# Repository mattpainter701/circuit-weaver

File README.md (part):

<p align="center">

</p>

<p align="center">
  <strong>Programmatic KiCad schematic generation, strict validation, and manufacturing export<br>
  designed for AI-assisted hardware workflows — Claude Code, Codex, and offline CLI.</strong>
</p>

---

## How It Works

The repository also hosts [Weftline 16](asic/slot16/README.md), an experimental embedded processor built on the Slot16 ISA. Its [virtual board](asic/slot16/virtual-board.md) runs the encoder firmware on a desktop with Python.

[Heddle](asic/heddle/README.md) is a second experimental tile: a character language model whose weights are hardwired as logic, with a PCI Express host-card draft and a study of what a much larger hardwired model would need.

Circuit Weaver supports **describe the design → validate → generate KiCad artifacts**, with additional native placement, routing and review workflows. Start from an agent skill or the CLI and inspect the resulting evidence and blockers before proceeding.

### Validated scope

Explore the [interactive routing demos](https://circuit-weaver.com/routing-demos/) to switch between placement and routed copper on three industrial prototype boards, then download the native KiCad files. The pictured Gateway, Relay and Setpoint routes passed KiCad 10.0.4 DRC with zero findings across boards ranging from 187 to 438 footprints.

Circuit Weaver is an **alpha tool for engineering prototypes**. The 0.37.0 workflow corpus covers 13 compact design-spec samples and three connected mixed-signal boards with 149, 155 and 145 physical parts. Each passes 16 stages, including native routing, DRC, assembled model previews and a real MCP session. These are finite regression fixtures; passing them does not establish arbitrary-circuit electrical correctness or fabrication readiness.

Claude Code, Codex and OpenCode can use the packaged agent skills, CLI and optional MCP server. MCP retains its five focused validation and discovery tools and adds runtime inspection plus checkpointed project lifecycle tools. Workflow execution is a synchronous request/response operation; cancellation is observed at stage boundaries. Installer and MCP tests do not constitute a fresh end-to-end test inside every agent client; see [agent platform support](docs/agent-platforms.md).

| Project workflow need | CLI | MCP | Behavior |
|-|-|-|-|
| Check the installed interpreter, capabilities and skill state | `runtime-info --json` | `runtime_info` | Read-only preflight |
| Discover or start a project | `discover --root <dir> --json`, `start <dir> --json` | `discover_projects`, `start_project` | Project paths are explicit for lifecycle operations |
| Open, inspect, and plan work | `open <path> --json`, `workflow plan <dir> --json` | `open_project`, `workflow_status`, `plan_workflow` | Planning does not execute stages |
| Execute or continue checkpointed work | `workflow run <dir>`, `workflow resume <dir>` | `run_workflow`, `resume_workflow` | Stages are validate, generate, build, place, route, preview; checkpoints use input and artifact hashes |
| Request cancellation | `workflow cancel <dir>` | `cancel_workflow` | Cancellation takes effect at the next stage boundary |

See the [project workflow guide](docs/project-workflows.md) for runtime selection, Python functions, MCP configuration, and checkpoint semantics. These tools report only the evidence their completed stages actually produced; they do not grant manufacturing approval.

RF research and circuit-generation assistance are available, but controlled-impedance routing, matching networks, antenna performance and RF stability require separate engineering verification. Native DRC and a rendered board are not evidence of RF performance. Review the [automation validation guide](docs/automation-validation.md) for prerequisites, evidence and prototype delivery gates.

### Reproducible passive SPICE benchmarks

`python benchmarks/diverse_systems/spice_suite.py --output <new-empty-directory>` runs independently defined IoT, SDR IQ, Butterworth, radar IF-bank, megohm/picofarad, and OT burden fixtures through the product SPICE exporter and runner, then compares parsed results with analytic oracles. Ngspice is discovered on `PATH` or selected with `CIRCUIT_WEAVER_NGSPICE` / `--ngspice <executable>`. The suite reports unverified when ngspice is unavailable and labels the OT comparator unverified; its negative controls and passive-model results do not qualify IC models, RF layout, PCB behavior, or manufacturing readiness. See [the benchmark guide](benchmarks/diverse_systems/README.md).

---

<!-- capability-registry:start -->
## Capability Contract

This table is generated from the checked-in capability registry. Regenerate it with `python scripts/gen_capability_docs.py`; do not edit it by hand.

Verification is conservative: a capability only claims the evidence level its public path actually verifies. **not applicable** means an operational capability makes no design-artifact verification claim; it is not a lower verification level.

| CLI capability | Maturity | Public surfaces | Verification contract | Evidence | Since |
|---|---|---|---|---|---|
| `validate` | beta | CLI: `validate`; Python: `circuit_weaver.dispatcher:validate_design`; HTTP: `POST /validate; POST /mvp/validate`; MCP: `validate_design`; Skill: `circuit-weaver` | `static-parse` → `static-parse` | `command-contract`, `static-parse` | 0.32.1 |
| `apply-patch` | beta | CLI: `apply-patch`; Python: `circuit_weaver.dispatcher:apply_design_patch`; HTTP: `POST /mvp/apply-patch` | `static-parse` → `static-parse` | `command-contract`, `static-parse` | 0.32.1 |
| `generate` | experimental | CLI: `generate`; Python: `circuit_weaver.dispatcher:generate_artifacts`; HTTP: `POST /generate; POST /mvp/generate`; MCP: `generate_artifacts`; Skill: `circuit-weaver` | `static-parse` → `static-parse` | `command-contract`, `static-parse`, `kicad-load`, `erc` | 0.32.1 |
| `review-report` | experimental | CLI: `review-report`; Skill: `circuit-weaver` | `static-parse` → `static-parse` | `command-contract`, `static-parse` | 0.32.1 |
| `diff` | beta | CLI: `diff`; Python: `circuit_weaver.dispatcher:diff_designs`; HTTP: `POST /mvp/diff` | `static-parse` → `static-parse` | `command-contract`, `static-parse` | 0.32.1 |
| `ingest-pcb-feedback` | beta | CLI: `ingest-pcb-feedback`; Python: `circuit_weaver.dispatcher:ingest_pcb_feedback`; HTTP: `POST /mvp/pcb-feedback` | `static-parse` → `static-parse` | `command-contract`, `static-parse` | 0.32.1 |
| `import-placement` | review_only | CLI: `import-placement`; Skill: `circuit-weaver` | `static-parse` → `static-parse` | `command-contract`, `static-parse` | 0.32.1 |
| `list-templates` | beta | CLI: `list-templates`; HTTP: `GET /templates` | not applicable (operational) | `command-contract` | 0.32.1 |
| `scaffold` | beta | CLI: `scaffold`; Skill: `circuit-weaver` | `static-parse` → `static-parse` | `command-contract`, `static-parse` | 0.32.1 |
| `register-ic` | experimental | CLI: `register-ic` | `static-parse` → `static-parse` | `command-contract`, `static-parse` | 0.32.1 |
| `resolve-symbol` | experimental | CLI: `resolve-symbol` | not applicable (operational) | `command-contract` | 0.33.0 |
| `adopt` | experimental | CLI: `adopt`; Python: `circuit_weaver.project_workflow:adopt_project`; MCP: `adopt_project`; Skill: `circuit-weaver` | not applicable (operational) | `command-contract` | 0.38.0 |
| `library-bundle` | experimental | CLI: `library-bundle`; Python: `circuit_weaver.library_bundle:plan_library_bundle`; MCP: `plan_library_bundle; apply_library_bundle`; Skill: `circuit-weaver` | not applicable (operational) | `command-contract` | 0.38.0 |
| `export-jlcpcb` | review_only | CLI: `export-jlcpcb`; Skill: `circuit-weaver` | `static-parse` → `static-parse` | `command-contract`, `static-parse` | 0.32.1 |
| `export-gerbers` | review_only | CLI: `export-gerbers`; Skill: `circuit-weaver` | `static-parse` → `static-parse` | `command-contract`, `static-parse` | 0.32.1 |
| `cost-bom` | experimental | CLI: `cost-bom`; Skill: `circuit-weaver` | `static-parse` → `static-parse` | `command-contract`, `static-parse` | 0.32.1 |
| `import-design` | experimental | CLI: `import-design`; Python: `circuit_weaver.design_import:import_design`; Skill: `circuit-weaver` | `static-parse` → `static-parse` | `command-contract`, `static-parse` | 0.32.1 |
| `analyze-design` | experimental | CLI: `analyze-design`; Python: `circuit_weaver.design_import:analyze_design`; Skill: `circuit-weaver` | `static-parse` → `static-parse` | `command-contract`, `static-parse` | 0.32.1 |
| `status` | beta | CLI: `status`; Python: `circuit_weaver.project_state:get_project_state_summary`; Skill: `circuit-weaver` | not applicable (operational) | `command-contract` | 0.32.1 |
| `resume` | experimental | CLI: `resume`; Python: `circuit_weaver.project_state:resume_project`; Skill: `circuit-weaver` | not applicable (operational) | `command-contract` | 0.32.1 |
| `design-wizard` | experimental | CLI: `design-wizard`; Skill: `design-wizard` | `static-parse` → `static-parse` | `command-contract`, `static-parse` | 0.32.1 |
| `build-pcb` | experimental | CLI: `build-pcb`; Python: `circuit_weaver.schematic_pcb:schematic_to_pcb`; Skill: `circuit-weaver` | `static-parse` → `kicad-load` | `command-contract`, `static-parse`, `kicad-load`, `external-tool` | 0.35.0 |
| `place-pcb` | experimental | CLI: `place-pcb`; Skill: `circuit-weaver` | `static-parse` → `static-parse` | `command-contract`, `external-tool`, `user-supplied` | 0.32.1 |
| `review-pcb` | review_only | CLI: `review-pcb`; Python: `circuit_weaver.board_review:review_pcb`; MCP: `review_board`; Skill: `circuit-weaver` | `static-parse` → `kicad-load` | `command-contract`, `external-tool`, `user-supplied` | 0.38.0 |
| `plane-pcb` | review_only | CLI: `plane-pcb`; Python: `circuit_weaver.pcb_ground_plane:add_ground_plane`; Skill: `circuit-weaver` | `static-parse` → `kicad-load` | `command-contract`, `kicad-load`, `external-tool`, `user-supplied` | 0.35.0 |
| `plane-cleanup-pcb` | review_only | CLI: `plane-cleanup-pcb`; Python: `circuit_weaver.pcb_plane_cleanup:cleanup_plane_traces`; Skill: `circuit-weaver` | `static-parse` → `kicad-load` | `command-contract`, `kicad-load`, `external-tool`, `user-supplied` | 0.35.0 |
| `cleanup-pcb` | review_only | CLI: `cleanup-pcb`; Python: `circuit_weaver.pcb_copper_cleanup:cleanup_copper`; Skill: `circuit-weaver` | `static-parse` → `kicad-load` | `command-contract`, `kicad-load`, `external-tool`, `user-supplied` | 0.35.0 |
| `refine-pcb` | review_only | CLI: `refine-pcb`; Python: `circuit_weaver.pcb_return_paths:refine_return_paths`; Skill: `circuit-weaver` | `static-parse` → `kicad-load` | `command-contract`, `kicad-load`, `external-tool`, `user-supplied` | 0.35.0 |
| `preview-pcb` | review_only | CLI: `preview-pcb`; Python: `circuit_weaver.pcb_preview:render_board_preview`; Skill: `circuit-weaver` | `static-parse` → `kicad-load` | `command-contract`, `static-parse`, `kicad-load`, `external-tool` | 0.35.0 |
| `log-status` | beta | CLI: `log-status` | not applicable (operational) | `command-contract` | 0.32.1 |
| `log-view` | beta | CLI: `log-view` | not applicable (operational) | `command-contract` | 0.32.1 |
| `autoroute` | review_only | CLI: `autoroute`; Skill: `circuit-weaver` | `static-parse` → `static-parse` | `command-contract`, `external-tool`, `user-supplied` | 0.32.1 |
| `install-skills` | experimental | CLI: `install-skills` | not applicable (operational) | `command-contract` | 0.32.1 |
| `schema` | beta | CLI: `schema` | not applicable (operational) | `command-contract` | 0.32.1 |
| `harvest-specs` | experimental | CLI: `harvest-specs` | `static-parse` → `static-parse` | `command-contract`, `external-tool` | 0.32.1 |
| `extract-specs` | experimental | CLI: `extract-specs` | `static-parse` → `static-parse` | `command-contract`, `user-supplied` | 0.32.1 |
| `fetch-spice` | experimental | CLI: `fetch-spice` | `static-parse` → `static-parse` | `command-contract`, `external-tool` | 0.32.1 |
| `cache` | beta | CLI: `cache` | not applicable (operational) | `command-contract` | 0.32.1 |
| `cache stats` | beta | CLI: `cache stats` | not applicable (operational) | `command-contract` | 0.32.1 |
| `cache clear` | review_only | CLI: `cache clear` | not applicable (operational) | `command-contract` | 0.32.1 |
| `optimize-placement` | review_only | CLI: `optimize-placement`; Skill: `circuit-weaver` | `static-parse` → `static-parse` | `command-contract`, `static-parse` | 0.32.1 |
| `placement-viewer` | review_only | CLI: `placement-viewer`; Skill: `circuit-weaver` | `static-parse` → `static-parse` | `command-contract`, `static-parse` | 0.32.1 |
| `si-constraints` | experimental | CLI: `si-constraints` | `static-parse` → `static-parse` | `command-contract`, `static-parse` | 0.32.1 |
| `thermal-analysis` | experimental | CLI: `thermal-analysis` | `static-parse` → `static-parse` | `command-contract`, `static-parse` | 0.32.1 |
| `export-dual-cpl` | review_only | CLI: `export-dual-cpl` | `static-parse` → `static-parse` | `command-contract`, `static-parse` | 0.32.1 |
| `panelize` | experimental | CLI: `panelize` | `static-parse` → `static-parse` | `command-contract`, `static-parse` | 0.32.1 |
| `design-enclosure` | experimental | CLI: `design-enclosure` | `static-parse` → `static-parse` | `command-contract`, `static-parse` | 0.32.1 |
| `check-dfm` | review_only | CLI: `check-dfm` | `static-parse` → `static-parse` | `command-contract`, `static-parse` | 0.32.1 |
| `generate-docs` | experimental | CLI: `generate-docs` | `static-parse` → `static-parse` | `command-contract`, `static-parse` | 0.32.1 |
| `erc` | review_only | CLI: `erc` | `kicad-load` → `erc` | `command-contract`, `kicad-load`, `erc` | 0.32.1 |
| `doctor` | beta | CLI: `doctor` | not applicable (operational) | `command-contract` | 0.32.1 |
| `repair` | experimental | CLI: `repair`; Python: `circuit_weaver.repair_service:apply_no_connect` | `static-parse` → `static-parse` | `command-contract`, `static-parse` | 0.35.0 |
| `confidence` | review_only | CLI: `confidence`; Skill: `circuit-weaver` | `static-parse` → `static-parse` | `command-contract`, `static-parse` | 0.32.1 |
| `manufacturing-readiness` | beta | CLI: `manufacturing-readiness`; Python: `circuit_weaver.manufacturing_readiness:read_manufacturing_readiness`; HTTP: `POST /manufacturing-readiness`; MCP: `manufacturing_readiness`; Skill: `circuit-weaver` | `static-parse` → `static-parse` | `command-contract`, `fabrication-ready` | 0.34.0 |
| `simulate` | experimental | CLI: `simulate`; Skill: `circuit-weaver` | `static-parse` → `static-parse` | `command-contract`, `static-parse` | 0.32.1 |
| `discover` | beta | CLI: `discover`; MCP: `discover_projects`; Skill: `circuit-weaver` | not applicable (operational) | `command-contract` | 0.32.1 |
| `start` | beta | CLI: `start`; Python: `circuit_weaver.project_workflow:start_project`; MCP: `start_project`; Skill: `circuit-weaver` | not applicable (operational) | `command-contract` | unreleased |
| `open` | beta | CLI: `open`; Python: `circuit_weaver.project_workflow:open_project`; MCP: `open_project`; Skill: `circuit-weaver` | not applicable (operational) | `command-contract` | unreleased |
| `runtime-info` | beta | CLI: `runtime-info`; Python: `circuit_weaver.runtime_info:runtime_info`; MCP: `runtime_info`; Skill: `circuit-weaver` | not applicable (operational) | `command-contract` | unreleased |
| `workflow` | beta | CLI: `workflow`; Skill: `circuit-weaver` | not applicable (operational) | `command-contract` | unreleased |
| `workflow plan` | beta | CLI: `workflow plan`; Python: `circuit_weaver.project_workflow:plan_workflow`; MCP: `plan_workflow`; Skill: `circuit-weaver` | not applicable (operational) | `command-contract` | unreleased |
| `workflow run` | beta | CLI: `workflow run`; Python: `circuit_weaver.project_workflow:run_workflow`; MCP: `run_workflow`; Skill: `circuit-weaver` | not applicable (operational) | `command-contract` | unreleased |
| `workflow status` | beta | CLI: `workflow status`; Python: `circuit_weaver.project_workflow:workflow_status`; MCP: `workflow_status`; Skill: `circuit-weaver` | not applicable (operational) | `command-contract` | unreleased |
| `workflow resume` | beta | CLI: `workflow resume`; Python: `circuit_weaver.project_workflow:resume_workflow`; MCP: `resume_workflow`; Skill: `circuit-weaver` | not applicable (operational) | `command-contract` | unreleased |
| `workflow cancel` | beta | CLI: `workflow cancel`; Python: `circuit_weaver.project_workflow:cancel_workflow`; MCP: `cancel_workflow`; Skill: `circuit-weaver` | not applicable (operational) | `command-contract` | unreleased |
| `library-access` | beta | CLI: `library-access`; Python: `circuit_weaver.library_access:audit_library_access`; MCP: `library_access`; Skill: `circuit-weaver` | not applicable (operational) | `command-contract` | unreleased |
| `silicon` | review_only | CLI: `silicon` | not applicable (operational) | `command-contract` | unreleased |
| `silicon preview` | review_only | CLI: `silicon preview`; Python: `circuit_weaver.silicon_preview:render_silicon_preview`; MCP: `silicon_preview` | `static-parse` → `static-parse` | `command-contract`, `external-tool`, `user-supplied` | unreleased |
| `silicon handoff` | review_only | CLI: `silicon handoff`; Python: `circuit_weaver.silicon_handoff:review_silicon_handoff`; MCP: `silicon_handoff` | `static-parse` → `static-parse` | `command-contract`, `external-tool`, `user-supplied` | unreleased |
| `silicon slot-map` | review_only | CLI: `silicon slot-map`; Python: `circuit_weaver.tt_slot:map_tt_slot`; MCP: `silicon_slot_map` | `static-parse` → `static-parse` | `command-contract`, `external-tool`, `user-supplied` | unreleased |
| `save-research` | experimental | CLI: `save-research`; Skill: `circuit-weaver` | `static-parse` → `static-parse` | `command-contract`, `static-parse` | 0.32.1 |
| `log-event` | beta | CLI: `log-event` | not applicable (operational) | `command-contract` | 0.32.1 |
<!-- capability-registry:end -->

## Quick Start

**Step 1 — Install**

```bash
pip install circuit-weaver
```

**Step 2 — Register the skill** *(one-time, for Claude Code / Codex / OpenCode)*

```bash
circuit-weaver install-skills            # install for all supported agent platforms
circuit-weaver install-skills --dry-run  # preview without touching disk
circuit-weaver install-skills --force --backup   # resolve conflicts, back up every replaced file
```

> **Upgrade safety:** each installed skill has a provenance manifest containing hashes for every
> managed file. A pristine older release upgrades automatically. A file changed or deleted by the
> user is preserved and reported as a conflict, and the command exits non-zero. Pass `--force`
> only after reviewing conflicts; add `--backup` to preserve every replaced file.

**Step 3 — Launch**

```text
# Claude Code:
/circuit-weaver

# Codex:
$circuit-weaver

# OpenCode: ask it to use circuit-weaver (loaded through its skill tool).

# Or run offline without any agent:
circuit-weaver design-wizard
```

The skill walks through IC selection, spec validation, schematic generation, and the electrical-PCB handoff.

For a repeatable real-tool demonstration, run `python scripts/validate_app_workflow.py --output ./workflow-evidence`.
The [automation validation guide](docs/automation-validation.md) describes native ERC/DRC evidence, optional MCP checks,
and the prototype/manufacturing boundary.

---

## Research Traceability

Agentic research runs are expected to persist their output into `output/research/`.
That directory is the source of truth for why an IC was chosen, which citations
backed it, and which backend produced the result.

For Codex / Claude / OpenCode workflows, Step 2 IC research should stay in the
current agent session. If a premium-research command would delegate to a
subagent or fails with a model/tool conflict, use the platform's native web
tools instead and persist the backend that actually ran.

```bash
# Check which backend and depth are active before research starts
circuit-weaver doctor

# Optional: force backend/depth selection for agent workflows
export CIRCUIT_WEAVER_RESEARCH_BACKEND=standard   # or sonar-pro / auto
export CIRCUIT_WEAVER_RESEARCH_DEPTH=fast         # or normal
# PowerShell: $env:CIRCUIT_WEAVER_RESEARCH_BACKEND="standard"
# PowerShell: $env:CIRCUIT_WEAVER_RESEARCH_DEPTH="fast"

# Persist a completed research result
circuit-weaver save-research --project-dir ./output --file research.json
```

Each saved run produces `{slug}.json`, `{slug}.md`, and `summary.md`, and the
matching `design.log` entry records the canonical JSON path for later audit.

---

## Branch Maintenance

Use `scripts/cleanup_branches.py` to audit stale local branches before pruning them.
The command is dry-run by default and only targets merged, unprotected branches,
so dated work can be reviewed without risking useful code. When run with
`--delete`, deleted branch tips are archived under `refs/archive/branches/<name>`
unless `--no-archive` is explicitly supplied.

```bash
python scripts/cleanup_branches.py                 # audit only
python scripts/cleanup_branches.py --delete        # prune merged stale branches and keep archives
python scripts/cleanup_branches.py --force-unmerged # include unmerged branches only when intentionally forced
```

---

## What You Get

A successful default `generate` run produces a complete artifact bundle
(`--no-placement-review` deliberately omits the four placement-review files):

| Artifact | File | Description |
|-|-|-|
| KiCad schematic hierarchy | `{project}.kicad_sch` plus functional sub-sheets | Real, loadable hierarchy; explicit block `section` values remain separate professional sheets and support passives follow their owner |
| Markdown design report | `{project}_report.md` | Validation results, component summary, and design notes |
| Placement review | `placement_result.json`, `placement_review_context.json`, `placement.svg`, `placement_editor.html` | Exhaustive, reference-reconciled heuristic proposal with review blockers and official-reference context; never fabrication data |
| Assembly inventory | `assembly_manifest.json` | Stable physical-part references, including generated support passives |
| Evidence ledger | `evidence_manifest.json` | Stable component, pinout, footprint, parameter, finding, tool, and verification provenance IDs |
| Canonical spec and IR | `canonical_spec.yaml`, `design_ir.json` | Normalized source of truth and generated design IR |
| Validation evidence | `validation_report.json`, `placement_readiness.json` | Machine-readable release/readiness checks |
| Artifact inventory | `artifact_manifest.json` | Portable relative paths, verification state, kinds, and sizes for every generated artifact |
| Test point map | `{project}_test_points.csv` | Auto-detected power, clock, bus, and differential-pair nets |
| Firmware stubs (when applicable) | `{project}_pinout.csv`, `.ioc`, `sdkconfig.defaults` | MCU pin map and STM32/ESP32 co-design files |

---

## Resume or Analyze an Existing Design

Circuit Weaver keeps restartable state in `<project>/.circuit-weaver/project.json`.
Import is non-destructive: source KiCad, PCB, Gerber, drill, and ZIP files are
inventoried and hashed rather than regenerated.

```bash
# Import a KiCad project, a single KiCad file, a Gerber directory, or a ZIP
circuit-weaver import-design ./existing_board --analyze

# Inspect durable state or get a deterministic restart plan
circuit-weaver status ./existing_board
circuit-weaver resume ./existing_board

# Re-run every applicable bundled analyzer; unchanged results are cached
circuit-weaver analyze-design ./existing_board
```

Use `--project-dir <dir>` when state should live somewhere other than the
source directory. Use `--force` only to intentionally replace a changed import
source set, ZIP staging tree, or cached analysis. Netlist-only imports are
inventoried, but analysis is reported as unsupported because a netlist alone
does not contain schematic or physical-layout evidence.

### Bounded no-connect repair

The first experimental imported-design repair is deliberately narrow: it can
add one explicit KiCad no-connect marker only when a
`circuit-weaver-repair-metadata/v1` envelope binds the exact source hash,
analyzer component/pin identity, a v2 finding, and its validated evidence
manifest. Build that envelope with
`circuit_weaver.repair_service.build_no_connect_metadata`; the matching trusted
finding producer is `no_connect_finding_from_intent`. Both require current,
verified user evidence whose exact `pin:REF.NUMBER` claim says the pin is
intentionally unused. Raw analyzer JSON or an unbound boolean is rejected.

The service then independently proves the component UUID/library ID, pin
coordinate, and absence of a net, wire, label, junction, bus entry,
hierarchical sheet pin, power symbol, or coincident component pin. The plan is
reviewable JSON; the apply step will not infer approval from that file.

```bash
circuit-weaver repair suggest board.kicad_sch repair-metadata.json \
  --ref U1 --pin 4 \
  --finding-id FND-0123456789ab \
  --evidence-id EV-VALIDATION-0123456789ab \
  --output no-connect-plan.json

# Review the plan and copy its plan_sha256 through the approval channel.
circuit-weaver repair apply no-connect-plan.json repair-metadata.json \
  --approved-plan-hash <approved-plan-sha256> \
  --reviewer <reviewer> \
  --finding-id FND-0123456789ab \
  --evidence-id EV-VALIDATION-0123456789ab

circuit-weaver repair verify board.kicad_sch no-connect-plan.json
```

The public capability guarantee is static parsing. Run KiCad ERC after review;
unsupported topology, geometry, part replacement, and pin-remapping repairs
fail closed instead of being improvised. Apply holds cross-process source and
audit locks, keeps an exact hard-linked preimage through publication, and uses
prepared/committed append-only audit events so an interrupted successful
publication can be recovered on retry. Lock hardlinks and reparse aliases are
rejected before mutation; the default audit sidecar cannot escape through a
directory junction. On Windows, atomic replacement preserves and verifies the
target owner, group, and DACL access semantics. Applications that write
schematics without honoring Circuit Weaver's lock remain outside the
cooperative locking contract; snapshot, identity, and post-image checks still
detect ordinary write races and preserve observed user bytes rather than
rolling over them.

---

## PCB Placement Workflow

Circuit Weaver generates a review-only placement proposal, then KiCad creates
the electrical PCB. The SVG/HTML/JSON proposal is never a PCB, CPL, or other
fabrication artifact.

### 1 — Generate initial placement

`generate` returns the path to `artifact_manifest.json`. Resolve that manifest's portable `root_schematic` and artifact paths relative to the manifest directory instead of guessing filenames. Check `verification_status` before claiming KiCad verification. Placement review is enabled by default:

```bash
circuit-weaver generate design.yaml -o ./output
# → output/{project}.kicad_sch
# → output/placement_result.json
# → output/placement_review_context.json
# → output/placement.svg
# → output/placement_editor.html
# → output/{project}_report.md
```

`placement_result.json` must contain the exact `assembly_manifest.json`
reference inventory. It remains `fabrication_ready: false` by design. Review
its overlap, boundary, support-part, geometry, sourcing, and constraint
blockers. `placement_review_context.json` records constraints, targeted
research prompts, and official component/reference-layout links available to
the agent; manufacturer documentation remains authoritative.

### 2 — Optimize with simulated annealing

```bash
# Basic optimization (5 000 iterations, reproducible with seed)
circuit-weaver optimize-placement design.yaml --iterations 5000 --seed 42 \
    -o output/placement.json

# Thermal-aware strategy (minimizes hotspot proximity)
circuit-weaver optimize-placement design.yaml --strategy thermal --iterations 10000 \
    -o output/placement.json

# Read component thermal/SI specs from YAML files
circuit-weaver optimize-placement design.yaml --specs-dir ./specs/
```

The optimizer minimizes: overlap, boundary violations, thermal clustering, and DFM zone penalties via simulated annealing. Returns a placement JSON with x/y/rotation/layer per component.

### 3 — Review in the interactive viewer

Open the generated `output/placement_editor.html`, or generate a standalone
viewer for a different optimizer configuration:

```bash
circuit-weaver placement-viewer design.yaml -o output/viewer.html
```

Opens a self-contained HTML file with:
- Click-to-highlight nets
- Component hover tooltips (value, footprint, MPN)
- Thermal heatmap overlay (blue → red gradient by power dissipation)
- CSV export button for placement data

### 4 — Create the electrical PCB in KiCad

Open `artifact_manifest.json`, then open its `root_schematic`, assign and verify footprints, and run **Update PCB from Schematic**. Save that electrically annotated board under a separate name. Only this board has the pads and nets required by routing, DFM, and Gerber export.

Apply reviewed SVG coordinates only to that real electrical PCB. The default
import is strict: every PCB reference must appear exactly once in the SVG, and
unexpected or missing references block the write.

```bash
circuit-weaver import-placement output/placement.svg board.kicad_pcb \
    -o board_placed.kicad_pcb --dry-run
circuit-weaver import-placement output/placement.svg board.kicad_pcb \
    -o board_placed.kicad_pcb

# Intentional subset update only; unknown SVG references still fail.
circuit-weaver import-placement subset.svg board.kicad_pcb \
    -o board_placed.kicad_pcb --allow-partial
```

### 5 — Place and route the real board

After forward annotation, add a rectangular Edge.Cuts outline and lock connectors
that must remain fixed. Place the actual library footprints, route, import the
tracks, and check the final PCB:

```bash
circuit-weaver place-pcb board.kicad_pcb -o board_placed.kicad_pcb --seed 7
circuit-weaver autoroute board_placed.kicad_pcb --attempts 3 \
    --routed-board board_routed.kicad_pcb
circuit-weaver preview-pcb board_routed.kicad_pcb -o board-preview.svg
```

The preview draws actual board layers and footprint body geometry. Use `--side back`
for a mirrored underside or `--render-3d` for a native assembly-model PNG on KiCad 9+
with the declared model files installed. The [workflow demo](docs/automation-validation.md)
includes named preview controls and full-size views.

KiCad's native Python is discovered separately from your application Python.
Freerouting and a compatible Java runtime are required for routing. The input
board must have real pads and nets; padless previews are rejected. Placement
currently requires an unrouted rectangular board without zones. It preserves
locked footprints and board sides, uses real courtyards and rotated pad locations,
and checks physical DRC. Routing publishes the final board only after KiCad DRC
passes, preserving project rules. See [setup and limits](docs/routing-placement-search.md).

For custom footprint installations, set `KICAD_FOOTPRINT_DIR` or the matching
`KICAD10_FOOTPRINT_DIR`, `KICAD9_FOOTPRINT_DIR`, or `KICAD8_FOOTPRINT_DIR`.
An explicit library root takes precedence. Known bare package names use the same
library-prefix mapping during validation and generation; custom references must
still resolve exactly.

Native placement permits overlapping front/back SMD body projections only when
the pad and copper-layer inventory proves separate surfaces and no opposite-side
courtyard is present. Through-hole and unknown geometry remain blocking. This
does not establish 3D enclosure clearance or signal integrity.

With complete native pad maps, decoupling refinement considers position and
quarter-turn rotation together around the owner's supply and return pads.
Candidates must improve the existing placement rank while preserving constraints,
board sides, both local power-leg distances and global power-net spans. These
geometric checks still require native label checks, routing and final DRC; they
do not establish routed loop inductance or electrical performance.

For imported boards with a legacy `.pro` project, convert and verify the project
rules in KiCad before placement, routing, or copper edits. These operations
require a sibling `.kicad_pro` when `.pro` exists; upgrading the PCB format alone
does not migrate those rules. Read-only inspection and previews remain available.

Each Freerouting attempt saves stdout, stderr, the actual input board design
(DSN), and an `attempt.json` manifest under `.circuit-weaver-router-logs` beside
the requested session. The manifest records the command and the input SHA-256.
Full logs stay on disk. Returned diagnostics use bounded windows and missing
final statistics remain unverified. The DSN contains the board geometry and
netlist. Keep this directory local when sharing a project.

PCB handoff manifests distinguish requested constraints from emitted KiCad rules.
DDR interfaces retain explicit unverified requirements for device timing,
topology, signal roles and stackup. Rule rendering and ordinary DRC do not
establish DDR timing closure or controlled impedance.

### 6 — DFM check and panelization

```bash
# Check static track/via dimensions; native KiCad DRC is also required
circuit-weaver check-dfm electrical_board.kicad_pcb --profile jlcpcb

# Get panel layout suggestions for small boards
circuit-weaver panelize --board-width 50 --board-height 40 --qty 100

# Export dual-sided CPL (top + bottom)
circuit-weaver export-dual-cpl design.yaml --pcb electrical_board.kicad_pcb -o ./jlcpcb

# Export a reconciled JLCPCB delivery and inspect its commit manifest
circuit-weaver export-jlcpcb design.yaml --pcb electrical_board.kicad_pcb -o ./jlcpcb
# → bom_jlcpcb.csv, cpl_jlcpcb.csv, README_jlcpcb.txt, delivery_manifest.json
```

Without `--pcb`, `export-jlcpcb` is intentionally BOM-only. A supplied board
must match every assembly reference and footprint before CPL publication.
Treat `delivery_manifest.json` as the delivery status/commit marker.

---

## CLI Reference

```bash
# ── Design lifecycle ──────────────────────────────────────────────────────────
circuit-weaver validate design.yaml               # Validate spec (no files written)
circuit-weaver generate design.yaml -o ./output  # Full artifact bundle
circuit-weaver erc output/{project}.kicad_sch      # Use root_schematic from artifact_manifest.json
circuit-weaver diff old.yaml new.yaml             # Semantic diff + optional SVG
circuit-weaver import-design ./legacy_board --analyze
circuit-weaver status ./legacy_board
circuit-weaver resume ./legacy_board
circuit-weaver analyze-design ./legacy_board

# ── Placement ─────────────────────────────────────────────────────────────────
circuit-weaver optimize-placement design.yaml --iterations 5000 --seed 42 -o output/placement.json
circuit-weaver placement-viewer design.yaml -o output/viewer.html
circuit-weaver import-placement placement.svg board.kicad_pcb -o out.kicad_pcb
circuit-weaver import-placement subset.svg board.kicad_pcb -o out.kicad_pcb --allow-partial
circuit-weaver check-dfm electrical_board.kicad_pcb --profile jlcpcb
circuit-weaver panelize --board-width 50 --board-height 40 --qty 100
circuit-weaver export-dual-cpl design.yaml --pcb electrical_board.kicad_pcb -o ./jlcpcb

# ── Simulation & confidence ──────────────────────────────────────────────────
circuit-weaver simulate design.yaml -o ./sims      # Run SPICE simulations (ngspice)
circuit-weaver confidence design.yaml --run-sims   # Full design readiness score (0-100)
circuit-weaver confidence design.yaml -o report.html --pcb board.kicad_pcb

# ── BOM and manufacturing ─────────────────────────────────────────────────────
circuit-weaver cost-bom design.yaml --qty 1,10,100
circuit-weaver export-jlcpcb design.yaml --pcb electrical_board.kicad_pcb -o ./jlcpcb
circuit-weaver export-gerbers electrical_board.kicad_pcb -o ./gerbers

# ── Project management ───────────────────────────────────────────────────────
circuit-weaver discover                             # Auto-detect projects in CWD
circuit-weaver discover --json --depth 2            # JSON output, search 2 levels deep
circuit-weaver save-research --project-dir ./output --file research.json
circuit-weaver log-event ./project --type scoring --message "Review done"
circuit-weaver doctor                               # Check credentials, backends, and tool availability

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
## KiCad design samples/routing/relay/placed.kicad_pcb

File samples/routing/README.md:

# KiCad routing samples

Open a **routed** board in KiCad 10 PCB Editor to inspect the copper, or use its
**placed** board to try a different routing policy on the same footprint and
reference-label positions. Keep each board beside its same-named `.kicad_pro`
so KiCad loads the original net classes. These are two-layer prototype layouts
for placement, routing and repair experiments.

| Board | What to inspect | KiCad files | Vias | Copper |
| --- | --- | --- | ---: | ---: |
| **Facility gateway** · 187 footprints | Eight analog acquisition channels share the board with RS-485 and CAN. The full and first-clean policies produced identical copper in all three paired runs. | [Placed](gateway/placed.kicad_pcb) · [Routed](gateway/routed.kicad_pcb) · [Project files](gateway/) | 214 | 10,328.81 mm |
| **Serial relay output card** · 268 footprints | Follow the register-to-driver-to-header routing on 160 coil channels. The pictured first-clean route used 19 more vias than its paired full-portfolio run. | [Placed](relay/placed.kicad_pcb) · [Routed](relay/routed.kicad_pcb) · [Project files](relay/) | 839 | 27,749.30 mm |
| **Analog setpoint card** · 438 footprints | Follow the shared SPI bus to 36 dual DACs and the filters serving 72 outputs. The saved partial below isolates one open on that bus. | [Placed](setpoint/placed.kicad_pcb) · [Routed](setpoint/routed.kicad_pcb) · [Project files](setpoint/) | 530 | 20,433.41 mm |

| Facility gateway | Serial relay | Analog setpoint |
| --- | --- | --- |
|  |  |  |

Orange traces are front copper and blue traces are back copper. Each preview
shows its linked routed file. The lengths above sum native track and arc
lengths on both layers. Each of these three files passed KiCad 10.0.4 DRC with
zero findings and passed its signal and return-path checks (43, 160 and 110
paths respectively).

## Replay a route

From the repository root, copy a placement and its project into an empty
working directory. This example uses Gateway. The study used KiCad 10.0.4
and Freerouting 2.5.0 with the following settings.

```sh
mkdir gateway-trial
cp samples/routing/gateway/placed.kicad_pcb gateway-trial/
cp samples/routing/gateway/placed.kicad_pro gateway-trial/
cd gateway-trial
circuit-weaver autoroute placed.kicad_pcb --routed-board result.kicad_pcb --attempts 3 --timeout 1800 --max-passes 20 --optimization-threads 0 --repair-open-connections --recovery-timeout 1800 --stop-at-first-clean
kicad-cli pcb drc --format json --severity-all --exit-code-violations -o result-drc.json result.kicad_pcb
```

For a full-portfolio comparison, repeat in a second empty directory with the
same inputs and omit `--stop-at-first-clean`. Independent runs can choose
different routes. The gallery preserves the representative first-clean outputs
from Gateway repeat 3, Relay repeat 1 and Setpoint repeat 3. The study reports
the medians across all three repeats. [Routing study and timings](https://github.com/mattpainter701/circuit-weaver/pull/63)
· [Tool setup](../../docs/routing-placement-search.md#tool-setup)

## Inspect the last Setpoint open

Open [last-open.kicad_pcb](setpoint/last-open.kicad_pcb) with its
[project settings](setpoint/last-open.kicad_pro). Run DRC and select the single
unconnected item to zoom to pad **U54.7** and the **F.Cu** track on
`SPI_MOSI`. This snapshot comes from repair of a partial session on the same
placement. It closed 107 of 108 opens. The independent clean route in the
gallery shows one way the full-board router connected that net.
[Compare the two SPI_MOSI routes at the same scale](setpoint/spi-mosi.svg)

From the repository root, replay stock repair with the remaining time budget.
The command writes fresh DRC and recovery evidence into a new directory.

```sh
python benchmarks/general_scale/replay_routing_repair.py samples/routing/setpoint/last-open.kicad_pcb --output setpoint-replay --recovery-seconds 104.4 --pair-limit 0
```

The recorded baseline ended with one open and zero other DRC findings. The
replay output records the remaining opens and whether a clean board was
published. [Repair study](https://github.com/mattpainter701/circuit-weaver/pull/64)
· [Replay options](../../benchmarks/general_scale/README.md#replay-routing-repair)

The designs and path contracts come from Circuit Weaver's
[unseen-scale fixtures](../../benchmarks/unseen_scale/README.md).
[SHA256SUMS](SHA256SUMS) identifies the exact PCB and project files in this gallery.

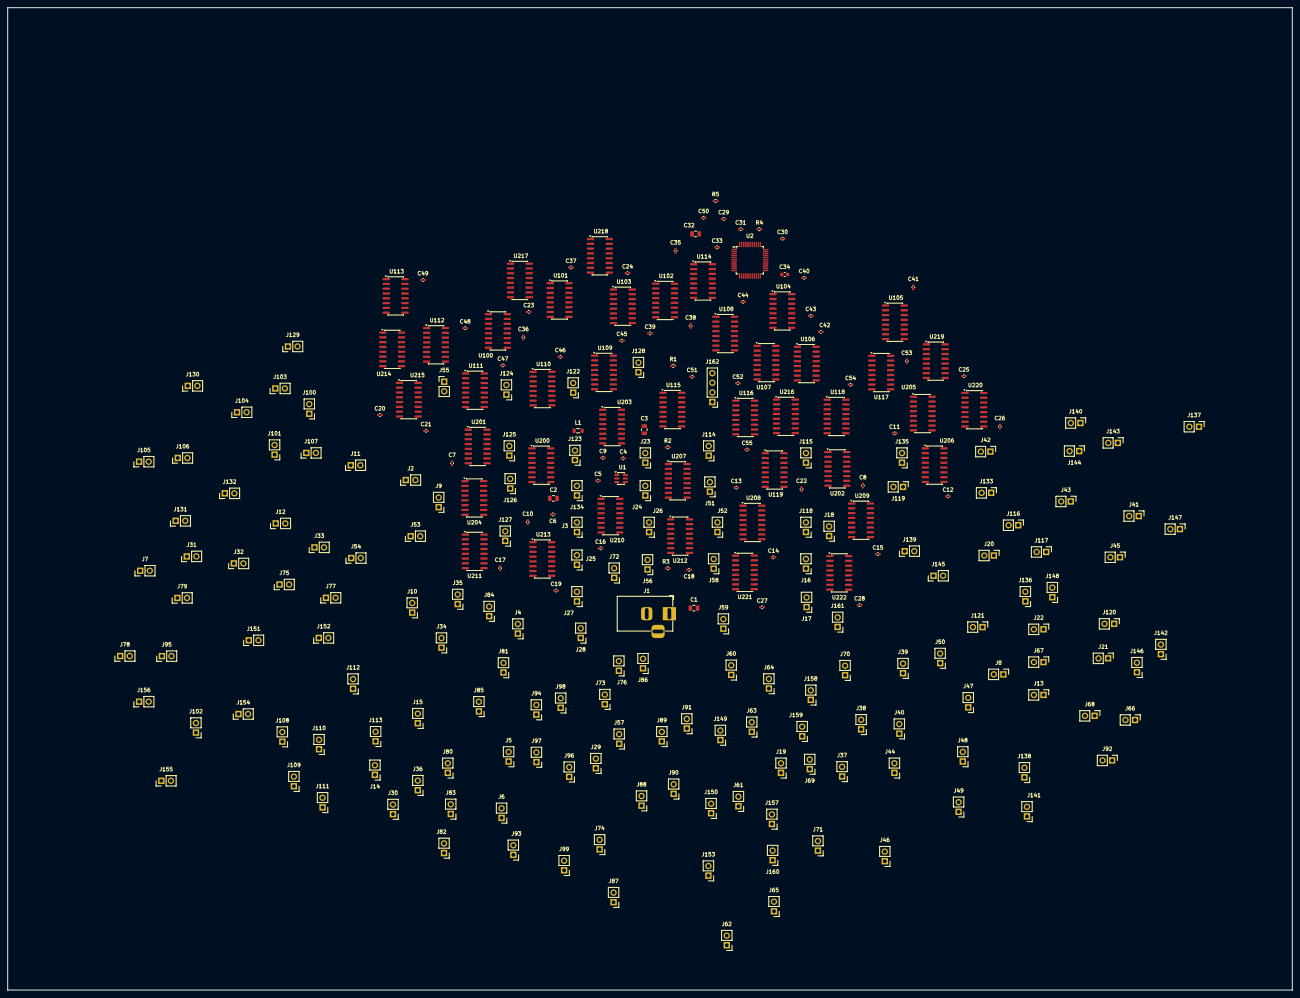
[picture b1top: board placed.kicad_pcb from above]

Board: 2 copper layers, 340.0 x 260.0 mm, 268 parts (0 on the bottom side), 353 nets, no tracks yet.

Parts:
C1, C2: 10uF; C_0805_2012Metric
C3: 6.2uF; C_0805_2012Metric
C4, C5, C6, C7, C8, C9, C10, C11, C12, C13, C14, C15, C16, C17, C18, C19, C20, C21, C22, C23, C24, C25, C26, C27, C28, C29, C30, C31, C35, C36, C37, C38, C39, C40, C41, C42, C43, C44, C45, C46, C47, C48, C49, C50, C51, C52, C53, C54, C55: 100nF; C_0402_1005Metric
C32: 4.7uF; C_0805_2012Metric
C33: 10nF; C_0402_1005Metric
C34: 1uF; C_0603_1608Metric
J1: BARREL_JACK_2.1MM; BarrelJack_Horizontal
J2, J3, J4, J5, J6, J7, J8, J9, J10, J11, J12, J13, J14, J15, J16, J17, J18, J19, J20, J21, J22, J23, J24, J25, J26, J27, J28, J29, J30, J31, J32, J33, J34, J35, J36, J37, J38, J39, J40, J41, J42, J43, J44, J45, J46, J47, J48, J49, J50, J51, J52, J53, J54, J55, J56, J57, J58, J59, J60, J61, J62, J63, J64, J65, J66, J67, J68, J69, J70, J71, J72, J73, J74, J75, J76, J77, J78, J79, J80, J81, J82, J83, J84, J85, J86, J87, J88, J89, J90, J91, J92, J93, J94, J95, J96, J97, J98, J99, J100, J101, J102, J103, J104, J105, J106, J107, J108, J109, J110, J111, J112, J113, J114, J115, J116, J117, J118, J119, J120, J121, J122, J123, J124, J125, J126, J127, J128, J129, J130, J131, J132, J133, J134, J135, J136, J137, J138, J139, J140, J141, J142, J143, J144, J145, J146, J147, J148, J149, J150, J151, J152, J153, J154, J155, J156, J157, J158, J159, J160, J161: PIN_HEADER_2P; PinHeader_1x02_P2.54mm_Vertical
J162: PIN_HEADER_4P; PinHeader_1x04_P2.54mm_Vertical
L1: 6.8uH; L_0805_2012Metric
R1, R4, R5: 10k; R_0402_1005Metric
R2: 357k; R_0402_1005Metric
R3: 115k; R_0402_1005Metric
U1: AP62300; SOT-23-6
U2: STM32F103C8T6; LQFP-48_7x7mm_P0.5mm
U100, U101, U102, U103, U104, U105, U106, U107, U108, U109, U110, U111, U112, U113, U114, U115, U116, U117, U118, U119: 74HC595D; SOIC-16_3.9x9.9mm_P1.27mm
U200, U201, U202, U203, U204, U205, U206, U207, U208, U209, U210, U211, U212, U213, U214, U215, U216, U217, U218, U219, U220, U221, U222: ULN2003A; SOIC-16_3.9x9.9mm_P1.27mm

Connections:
BOOT0: R4.1, U2.44
BST_U1: C4.2, U1.6
COIL_DRV_U200_1: U100.15, U200.1
COIL_DRV_U200_2: U100.1, U200.2
COIL_DRV_U200_3: U100.2, U200.3
COIL_DRV_U200_4: U100.3, U200.4
COIL_DRV_U200_5: U100.4, U200.5
COIL_DRV_U200_6: U100.5, U200.6
COIL_DRV_U200_7: U100.6, U200.7
COIL_DRV_U201_1: U100.7, U201.1
COIL_DRV_U201_2: U101.15, U201.2
COIL_DRV_U201_3: U101.1, U201.3
COIL_DRV_U201_4: U101.2, U201.4
COIL_DRV_U201_5: U101.3, U201.5
COIL_DRV_U201_6: U101.4, U201.6
COIL_DRV_U201_7: U101.5, U201.7
COIL_DRV_U202_1: U101.6, U202.1
COIL_DRV_U202_2: U101.7, U202.2
COIL_DRV_U202_3: U102.15, U202.3
COIL_DRV_U202_4: U102.1, U202.4
COIL_DRV_U202_5: U102.2, U202.5
COIL_DRV_U202_6: U102.3, U202.6
COIL_DRV_U202_7: U102.4, U202.7
COIL_DRV_U203_1: U102.5, U203.1
COIL_DRV_U203_2: U102.6, U203.2
COIL_DRV_U203_3: U102.7, U203.3
COIL_DRV_U203_4: U103.15, U203.4
COIL_DRV_U203_5: U103.1, U203.5
COIL_DRV_U203_6: U103.2, U203.6
COIL_DRV_U203_7: U103.3, U203.7
COIL_DRV_U204_1: U103.4, U204.1
COIL_DRV_U204_2: U103.5, U204.2
COIL_DRV_U204_3: U103.6, U204.3
COIL_DRV_U204_4: U103.7, U204.4
COIL_DRV_U204_5: U104.15, U204.5
COIL_DRV_U204_6: U104.1, U204.6
COIL_DRV_U204_7: U104.2, U204.7
COIL_DRV_U205_1: U104.3, U205.1
COIL_DRV_U205_2: U104.4, U205.2
COIL_DRV_U205_3: U104.5, U205.3
COIL_DRV_U205_4: U104.6, U205.4
COIL_DRV_U205_5: U104.7, U205.5
COIL_DRV_U205_6: U105.15, U205.6
COIL_DRV_U205_7: U105.1, U205.7
COIL_DRV_U206_1: U105.2, U206.1
COIL_DRV_U206_2: U105.3, U206.2
COIL_DRV_U206_3: U105.4, U206.3
COIL_DRV_U206_4: U105.5, U206.4
COIL_DRV_U206_5: U105.6, U206.5
COIL_DRV_U206_6: U105.7, U206.6
COIL_DRV_U206_7: U106.15, U206.7
COIL_DRV_U207_1: U106.1, U207.1
COIL_DRV_U207_2: U106.2, U207.2
COIL_DRV_U207_3: U106.3, U207.3
COIL_DRV_U207_4: U106.4, U207.4
COIL_DRV_U207_5: U106.5, U207.5
COIL_DRV_U207_6: U106.6, U207.6
COIL_DRV_U207_7: U106.7, U207.7
COIL_DRV_U208_1: U107.15, U208.1
COIL_DRV_U208_2: U107.1, U208.2
COIL_DRV_U208_3: U107.2, U208.3
COIL_DRV_U208_4: U107.3, U208.4
COIL_DRV_U208_5: U107.4, U208.5
COIL_DRV_U208_6: U107.5, U208.6
COIL_DRV_U208_7: U107.6, U208.7
COIL_DRV_U209_1: U107.7, U209.1
COIL_DRV_U209_2: U108.15, U209.2
COIL_DRV_U209_3: U108.1, U209.3
COIL_DRV_U209_4: U108.2, U209.4
COIL_DRV_U209_5: U108.3, U209.5
COIL_DRV_U209_6: U108.4, U209.6
COIL_DRV_U209_7: U108.5, U209.7
COIL_DRV_U210_1: U108.6, U210.1
COIL_DRV_U210_2: U108.7, U210.2
COIL_DRV_U210_3: U109.15, U210.3
COIL_DRV_U210_4: U109.1, U210.4
COIL_DRV_U210_5: U109.2, U210.5
COIL_DRV_U210_6: U109.3, U210.6
COIL_DRV_U210_7: U109.4, U210.7
COIL_DRV_U211_1: U109.5, U211.1
COIL_DRV_U211_2: U109.6, U211.2
COIL_DRV_U211_3: U109.7, U211.3
COIL_DRV_U211_4: U110.15, U211.4
COIL_DRV_U211_5: U110.1, U211.5
COIL_DRV_U211_6: U110.2, U211.6
COIL_DRV_U211_7: U110.3, U211.7
COIL_DRV_U212_1: U110.4, U212.1
COIL_DRV_U212_2: U110.5, U212.2
COIL_DRV_U212_3: U110.6, U212.3
COIL_DRV_U212_4: U110.7, U212.4
COIL_DRV_U212_5: U111.15, U212.5
COIL_DRV_U212_6: U111.1, U212.6
COIL_DRV_U212_7: U111.2, U212.7
COIL_DRV_U213_1: U111.3, U213.1
COIL_DRV_U213_2: U111.4, U213.2
COIL_DRV_U213_3: U111.5, U213.3
COIL_DRV_U213_4: U111.6, U213.4
COIL_DRV_U213_5: U111.7, U213.5
COIL_DRV_U213_6: U112.15, U213.6
COIL_DRV_U213_7: U112.1, U213.7
COIL_DRV_U214_1: U112.2, U214.1
COIL_DRV_U214_2: U112.3, U214.2
COIL_DRV_U214_3: U112.4, U214.3
COIL_DRV_U214_4: U112.5, U214.4
COIL_DRV_U214_5: U112.6, U214.5
COIL_DRV_U214_6: U112.7, U214.6
COIL_DRV_U214_7: U113.15, U214.7
COIL_DRV_U215_1: U113.1, U215.1
COIL_DRV_U215_2: U113.2, U215.2
COIL_DRV_U215_3: U113.3, U215.3
COIL_DRV_U215_4: U113.4, U215.4
COIL_DRV_U215_5: U113.5, U215.5
COIL_DRV_U215_6: U113.6, U215.6
COIL_DRV_U215_7: U113.7, U215.7
COIL_DRV_U216_1: U114.15, U216.1
COIL_DRV_U216_2: U114.1, U216.2
COIL_DRV_U216_3: U114.2, U216.3
COIL_DRV_U216_4: U114.3, U216.4
COIL_DRV_U216_5: U114.4, U216.5
COIL_DRV_U216_6: U114.5, U216.6
COIL_DRV_U216_7: U114.6, U216.7
COIL_DRV_U217_1: U114.7, U217.1
COIL_DRV_U217_2: U115.15, U217.2
COIL_DRV_U217_3: U115.1, U217.3
COIL_DRV_U217_4: U115.2, U217.4
COIL_DRV_U217_5: U115.3, U217.5
COIL_DRV_U217_6: U115.4, U217.6
COIL_DRV_U217_7: U115.5, U217.7
COIL_DRV_U218_1: U115.6, U218.1
COIL_DRV_U218_2: U115.7, U218.2
COIL_DRV_U218_3: U116.15, U218.3
COIL_DRV_U218_4: U116.1, U218.4
COIL_DRV_U218_5: U116.2, U218.5
COIL_DRV_U218_6: U116.3, U218.6
COIL_DRV_U218_7: U116.4, U218.7
COIL_DRV_U219_1: U116.5, U219.1
COIL_DRV_U219_2: U116.6, U219.2
COIL_DRV_U219_3: U116.7, U219.3
COIL_DRV_U219_4: U117.15, U219.4
COIL_DRV_U219_5: U117.1, U219.5
COIL_DRV_U219_6: U117.2, U219.6
COIL_DRV_U219_7: U117.3, U219.7
COIL_DRV_U220_1: U117.4, U220.1
COIL_DRV_U220_2: U117.5, U220.2
COIL_DRV_U220_3: U117.6, U220.3
COIL_DRV_U220_4: U117.7, U220.4
COIL_DRV_U220_5: U118.15, U220.5
COIL_DRV_U220_6: U118.1, U220.6
COIL_DRV_U220_7: U118.2, U220.7
COIL_DRV_U221_1: U118.3, U221.1
COIL_DRV_U221_2: U118.4, U221.2
COIL_DRV_U221_3: U118.5, U221.3
COIL_DRV_U221_4: U118.6, U221.4
COIL_DRV_U221_5: U118.7, U221.5
COIL_DRV_U221_6: U119.15, U221.6
COIL_DRV_U221_7: U119.1, U221.7
COIL_DRV_U222_1: U119.2, U222.1
COIL_DRV_U222_2: U119.3, U222.2
COIL_DRV_U222_3: U119.4, U222.3
COIL_DRV_U222_4: U119.5, U222.4
COIL_DRV_U222_5: U119.6, U222.5
COIL_DRV_U222_6: U119.7, U222.6
FB_U1: R2.1, R3.2, U1.4
GND: C1.2, C2.1, C3.1, C5.2, C6.1, C7.1, C8.1, C9.1, C10.1, C11.1, C12.1, C13.1, C14.1, C15.1, C16.1, C17.1, C18.1, C19.1, C20.1, C21.1, C22.1, C23.1, C24.1, C25.1, C26.1, C27.1, C28.1, C29.1, C30.1, C31.1, C32.1, C33.1, C34.1, C35.2, C36.2, C37.2, C38.2, C39.2, C40.2, C41.2, C42.2, C43.2, C44.2, C45.2, C46.2, C47.2, C48.2, C49.2, C50.2, C51.2, C52.2, C53.2, C54.2, C55.2, J1.2, J1.3, J162.2, R3.1, R4.2, U1.1, U2.8, U2.23, U2.35, U2.47, U100.8, U100.13, U101.8, U101.13, U102.8, U102.13, U103.8, U103.13, U104.8, U104.13, U105.8, U105.13, U106.8, U106.13, U107.8, U107.13, U108.8, U108.13, U109.8, U109.13, U110.8, U110.13, U111.8, U111.13, U112.8, U112.13, U113.8, U113.13, U114.8, U114.13, U115.8, U115.13, U116.8, U116.13, U117.8, U117.13, U118.8, U118.13, U119.8, U119.13, U200.8, U201.8, U202.8, U203.8, U204.8, U205.8, U206.8, U207.8, U208.8, U209.8, U210.8, U211.8, U212.8, U213.8, U214.8, U215.8, U216.8, U217.8, U218.8, U219.8, U220.8, U221.8, U222.8
LOAD_U200_1: J2.2, U200.16
LOAD_U200_2: J3.2, U200.15
LOAD_U200_3: J4.2, U200.14
LOAD_U200_4: J5.2, U200.13
LOAD_U200_5: J6.2, U200.12
LOAD_U200_6: J7.2, U200.11
LOAD_U200_7: J8.2, U200.10
LOAD_U201_1: J9.2, U201.16
LOAD_U201_2: J10.2, U201.15
LOAD_U201_3: J11.2, U201.14
LOAD_U201_4: J12.2, U201.13
LOAD_U201_5: J13.2, U201.12
LOAD_U201_6: J14.2, U201.11
LOAD_U201_7: J15.2, U201.10
LOAD_U202_1: J16.2, U202.16
LOAD_U202_2: J17.2, U202.15
LOAD_U202_3: J18.2, U202.14
LOAD_U202_4: J19.2, U202.13
LOAD_U202_5: J20.2, U202.12
LOAD_U202_6: J21.2, U202.11
LOAD_U202_7: J22.2, U202.10
LOAD_U203_1: J23.2, U203.16
LOAD_U203_2: J24.2, U203.15
LOAD_U203_3: J25.2, U203.14
LOAD_U203_4: J26.2, U203.13
LOAD_U203_5: J27.2, U203.12
LOAD_U203_6: J28.2, U203.11
LOAD_U203_7: J29.2, U203.10
LOAD_U204_1: J30.2, U204.16
LOAD_U204_2: J31.2, U204.15
LOAD_U204_3: J32.2, U204.14
LOAD_U204_4: J33.2, U204.13
LOAD_U204_5: J34.2, U204.12
LOAD_U204_6: J35.2, U204.11
LOAD_U204_7: J36.2, U204.10
LOAD_U205_1: J37.2, U205.16
LOAD_U205_2: J38.2, U205.15
LOAD_U205_3: J39.2, U205.14
LOAD_U205_4: J40.2, U205.13
LOAD_U205_5: J41.2, U205.12
LOAD_U205_6: J42.2, U205.11
LOAD_U205_7: J43.2, U205.10
LOAD_U206_1: J44.2, U206.16
LOAD_U206_2: J45.2, U206.15
LOAD_U206_3: J46.2, U206.14
LOAD_U206_4: J47.2, U206.13
LOAD_U206_5: J48.2, U206.12
LOAD_U206_6: J49.2, U206.11
LOAD_U206_7: J50.2, U206.10
LOAD_U207_1: J51.2, U207.16
LOAD_U207_2: J52.2, U207.15
LOAD_U207_3: J53.2, U207.14
LOAD_U207_4: J54.2, U207.13
LOAD_U207_5: J55.2, U207.12
LOAD_U207_6: J56.2, U207.11
LOAD_U207_7: J57.2, U207.10
LOAD_U208_1: J58.2, U208.16
LOAD_U208_2: J59.2, U208.15
LOAD_U208_3: J60.2, U208.14
LOAD_U208_4: J61.2, U208.13
LOAD_U208_5: J62.2, U208.12
LOAD_U208_6: J63.2, U208.11
LOAD_U208_7: J64.2, U208.10
LOAD_U209_1: J65.2, U209.16
LOAD_U209_2: J66.2, U209.15
LOAD_U209_3: J67.2, U209.14
LOAD_U209_4: J68.2, U209.13
LOAD_U209_5: J69.2, U209.12
LOAD_U209_6: J70.2, U209.11
LOAD_U209_7: J71.2, U209.10
LOAD_U210_1: J72.2, U210.16
LOAD_U210_2: J73.2, U210.15
LOAD_U210_3: J74.2, U210.14
LOAD_U210_4: J75.2, U210.13
LOAD_U210_5: J76.2, U210.12
LOAD_U210_6: J77.2, U210.11
LOAD_U210_7: J78.2, U210.10
LOAD_U211_1: J79.2, U211.16
LOAD_U211_2: J80.2, U211.15
LOAD_U211_3: J81.2, U211.14
LOAD_U211_4: J82.2, U211.13
LOAD_U211_5: J83.2, U211.12
LOAD_U211_6: J84.2, U211.11
LOAD_U211_7: J85.2, U211.10
LOAD_U212_1: J86.2, U212.16
LOAD_U212_2: J87.2, U212.15
LOAD_U212_3: J88.2, U212.14
LOAD_U212_4: J89.2, U212.13
LOAD_U212_5: J90.2, U212.12
LOAD_U212_6: J91.2, U212.11
LOAD_U212_7: J92.2, U212.10
LOAD_U213_1: J93.2, U213.16
LOAD_U213_2: J94.2, U213.15
LOAD_U213_3: J95.2, U213.14
LOAD_U213_4: J96.2, U213.13
LOAD_U213_5: J97.2, U213.12
LOAD_U213_6: J98.2, U213.11
LOAD_U213_7: J99.2, U213.10
LOAD_U214_1: J100.2, U214.16
LOAD_U214_2: J101.2, U214.15
LOAD_U214_3: J102.2, U214.14
LOAD_U214_4: J103.2, U214.13
LOAD_U214_5: J104.2, U214.12
LOAD_U214_6: J105.2, U214.11
LOAD_U214_7: J106.2, U214.10
LOAD_U215_1: J107.2, U215.16
LOAD_U215_2: J108.2, U215.15
LOAD_U215_3: J109.2, U215.14
LOAD_U215_4: J110.2, U215.13
LOAD_U215_5: J111.2, U215.12
LOAD_U215_6: J112.2, U215.11
LOAD_U215_7: J113.2, U215.10
LOAD_U216_1: J114.2, U216.16
LOAD_U216_2: J115.2, U216.15
LOAD_U216_3: J116.2, U216.14
LOAD_U216_4: J117.2, U216.13
LOAD_U216_5: J118.2, U216.12
LOAD_U216_6: J119.2, U216.11
LOAD_U216_7: J120.2, U216.10
LOAD_U217_1: J121.2, U217.16
LOAD_U217_2: J122.2, U217.15
LOAD_U217_3: J123.2, U217.14
LOAD_U217_4: J124.2, U217.13
LOAD_U217_5: J125.2, U217.12
LOAD_U217_6: J126.2, U217.11
LOAD_U217_7: J127.2, U217.10
LOAD_U218_1: J128.2, U218.16
LOAD_U218_2: J129.2, U218.15
LOAD_U218_3: J130.2, U218.14
LOAD_U218_4: J131.2, U218.13
LOAD_U218_5: J132.2, U218.12
LOAD_U218_6: J133.2, U218.11
LOAD_U218_7: J134.2, U218.10
LOAD_U219_1: J135.2, U219.16
LOAD_U219_2: J136.2, U219.15
LOAD_U219_3: J137.2, U219.14
LOAD_U219_4: J138.2, U219.13
LOAD_U219_5: J139.2, U219.12
LOAD_U219_6: J140.2, U219.11
LOAD_U219_7: J141.2, U219.10
LOAD_U220_1: J142.2, U220.16
LOAD_U220_2: J143.2, U220.15
LOAD_U220_3: J144.2, U220.14
LOAD_U220_4: J145.2, U220.13
LOAD_U220_5: J146.2, U220.12
LOAD_U220_6: J147.2, U220.11
LOAD_U220_7: J148.2, U220.10
LOAD_U221_1: J149.2, U221.16
LOAD_U221_2: J150.2, U221.15
LOAD_U221_3: J151.2, U221.14
LOAD_U221_4: J152.2, U221.13
LOAD_U221_5: J153.2, U221.12
LOAD_U221_6: J154.2, U221.11
LOAD_U221_7: J155.2, U221.10
LOAD_U222_1: J156.2, U222.16
LOAD_U222_2: J157.2, U222.15
LOAD_U222_3: J158.2, U222.14
LOAD_U222_4: J159.2, U222.13
LOAD_U222_5: J160.2, U222.12
LOAD_U222_6: J161.2, U222.11
OUTPUT_ENABLE_N: R1.2, U2.13
RESET_N: C35.1, R5.1, U2.7
SHIFT_CLOCK: U2.11, U100.11, U101.11, U102.11, U103.11, U104.11, U105.11, U106.11, U107.11, U108.11, U109.11, U110.11, U111.11, U112.11, U113.11, U114.11, U115.11, U116.11, U117.11, U118.11, U119.11
SHIFT_DATA: U2.10, U100.14
SHIFT_LATCH: U2.12, U100.12, U101.12, U102.12, U103.12, U104.12, U105.12, U106.12, U107.12, U108.12, U109.12, U110.12, U111.12, U112.12, U113.12, U114.12, U115.12, U116.12, U117.12, U118.12, U119.12
SHIFT_QH_1: U100.9, U101.14
SHIFT_QH_2: U101.9, U102.14
SHIFT_QH_3: U102.9, U103.14
SHIFT_QH_4: U103.9, U104.14
SHIFT_QH_5: U104.9, U105.14
SHIFT_QH_6: U105.9, U106.14
SHIFT_QH_7: U106.9, U107.14
SHIFT_QH_8: U107.9, U108.14
SHIFT_QH_9: U108.9, U109.14
SHIFT_QH_10: U109.9, U110.14
SHIFT_QH_11: U110.9, U111.14
SHIFT_QH_12: U111.9, U112.14
SHIFT_QH_13: U112.9, U113.14
SHIFT_QH_14: U113.9, U114.14
SHIFT_QH_15: U114.9, U115.14
SHIFT_QH_16: U115.9, U116.14
SHIFT_QH_17: U116.9, U117.14
SHIFT_QH_18: U117.9, U118.14
SHIFT_QH_19: U118.9, U119.14
SWCLK: J162.4, U2.37
SWDIO: J162.3, U2.34
SW_U1: C4.1, L1.1, U1.2
VDD_3P3: C3.2, C29.2, C30.2, C31.2, C32.2, C33.2, C34.2, C36.1, C37.1, C38.1, C39.1, C40.1, C41.1, C42.1, C43.1, C44.1, C45.1, C46.1, C47.1, C48.1, C49.1, C50.1, C51.1, C52.1, C53.1, C54.1, C55.1, J162.1, L1.2, R1.1, R2.2, R5.2, U2.1, U2.9, U2.24, U2.36, U2.48, U100.10, U100.16, U101.10, U101.16, U102.10, U102.16, U103.10, U103.16, U104.10, U104.16, U105.10, U105.16, U106.10, U106.16, U107.10, U107.16, U108.10, U108.16, U109.10, U109.16, U110.10, U110.16, U111.10, U111.16, U112.10, U112.16, U113.10, U113.16, U114.10, U114.16, U115.10, U115.16, U116.10, U116.16, U117.10, U117.16, U118.10, U118.16, U119.10, U119.16
VIN_12V: C1.1, C2.2, C5.1, C6.2, C7.2, C8.2, C9.2, C10.2, C11.2, C12.2, C13.2, C14.2, C15.2, C16.2, C17.2, C18.2, C19.2, C20.2, C21.2, C22.2, C23.2, C24.2, C25.2, C26.2, C27.2, C28.2, J1.1, J2.1, J3.1, J4.1, J5.1, J6.1, J7.1, J8.1, J9.1, J10.1, J11.1, J12.1, J13.1, J14.1, J15.1, J16.1, J17.1, J18.1, J19.1, J20.1, J21.1, J22.1, J23.1, J24.1, J25.1, J26.1, J27.1, J28.1, J29.1, J30.1, J31.1, J32.1, J33.1, J34.1, J35.1, J36.1, J37.1, J38.1, J39.1, J40.1, J41.1, J42.1, J43.1, J44.1, J45.1, J46.1, J47.1, J48.1, J49.1, J50.1, J51.1, J52.1, J53.1, J54.1, J55.1, J56.1, J57.1, J58.1, J59.1, J60.1, J61.1, J62.1, J63.1, J64.1, J65.1, J66.1, J67.1, J68.1, J69.1, J70.1, J71.1, J72.1, J73.1, J74.1, J75.1, J76.1, J77.1, J78.1, J79.1, J80.1, J81.1, J82.1, J83.1, J84.1, J85.1, J86.1, J87.1, J88.1, J89.1, J90.1, J91.1, J92.1, J93.1, J94.1, J95.1, J96.1, J97.1, J98.1, J99.1, J100.1, J101.1, J102.1, J103.1, J104.1, J105.1, J106.1, J107.1, J108.1, J109.1, J110.1, J111.1, J112.1, J113.1, J114.1, J115.1, J116.1, J117.1, J118.1, J119.1, J120.1, J121.1, J122.1, J123.1, J124.1, J125.1, J126.1, J127.1, J128.1, J129.1, J130.1, J131.1, J132.1, J133.1, J134.1, J135.1, J136.1, J137.1, J138.1, J139.1, J140.1, J141.1, J142.1, J143.1, J144.1, J145.1, J146.1, J147.1, J148.1, J149.1, J150.1, J151.1, J152.1, J153.1, J154.1, J155.1, J156.1, J157.1, J158.1, J159.1, J160.1, J161.1, U1.3, U200.9, U201.9, U202.9, U203.9, U204.9, U205.9, U206.9, U207.9, U208.9, U209.9, U210.9, U211.9, U212.9, U213.9, U214.9, U215.9, U216.9, U217.9, U218.9, U219.9, U220.9, U221.9, U222.9

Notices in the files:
README.md:
License:
MIT. See [LICENSE](LICENSE).
